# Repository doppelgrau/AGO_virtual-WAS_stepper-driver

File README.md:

# AGO_virtual-WAS_stepper-driver

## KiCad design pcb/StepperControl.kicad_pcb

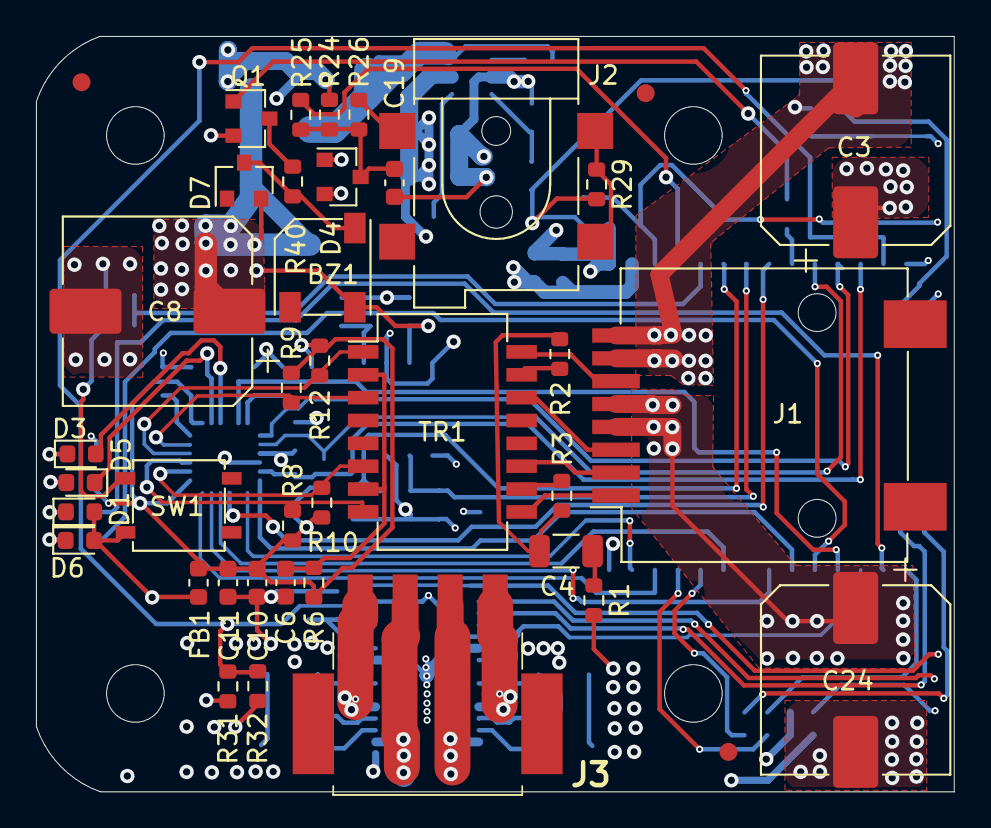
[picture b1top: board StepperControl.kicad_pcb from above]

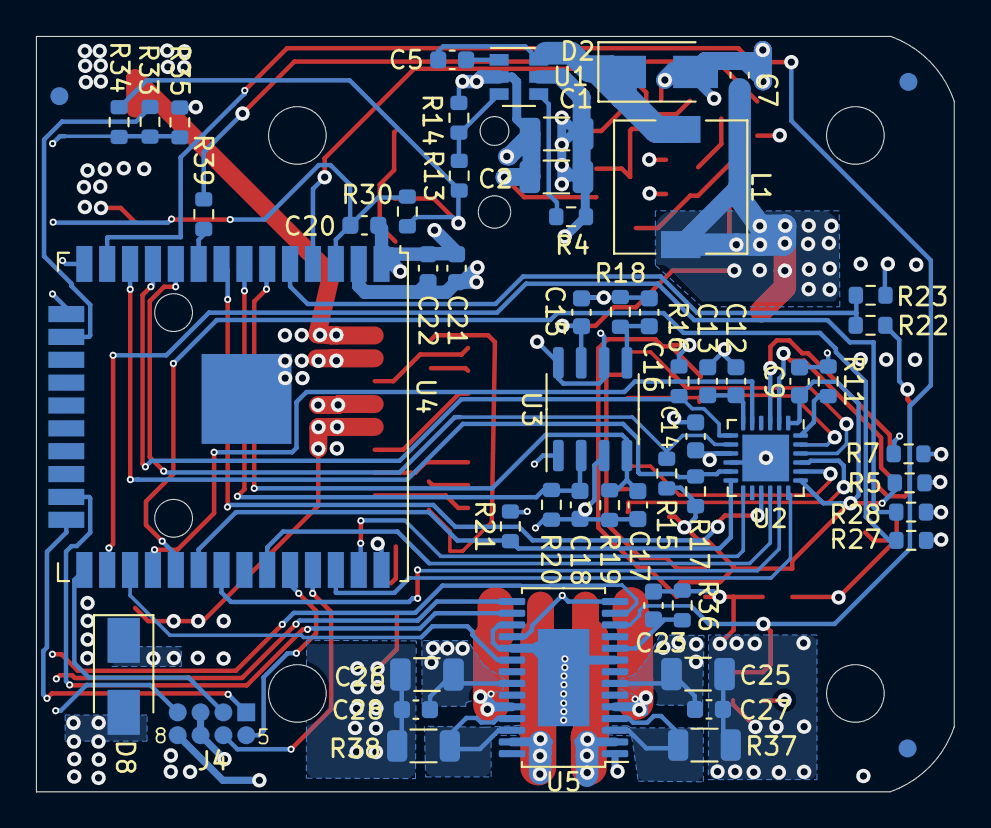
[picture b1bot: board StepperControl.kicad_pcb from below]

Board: 4 copper layers, 51.0 x 42.0 mm, 101 parts (57 on the bottom side), 72 nets.

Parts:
BZ1: SOUND-LD-BZEL-T56-0505; Loudity_SMT56
C1, C25, C26: CAP-X7R-1206-1uF-50V; C_1206_3216Metric
C2: CAP-X5R-1206-10uF-50V; C_1206_3216Metric
C3, C24: CAP-ALU-SMD-220uF-35V; CP_Elec_10x10
C4: CAP-X7R-1206-1nF-2kV; C_1206_3216Metric
C5, C6, C9, C11, C12, C14, C15, C20, C22, C27, C28: CAP-X7R-0603-100nF-50V; C_0603_1608Metric
C7, C10, C13, C21: CAP-X5R-0603-10uF-10V; C_0603_1608Metric
C8: CAP-ALU-SMD-1mF-10V; CP_Elec_10x10
C16, C17, C18, C19, C23: CAP-X7R-0603-1nF-50V; C_0603_1608Metric
D1: LED-0603-GREEN; LED_0603_1608Metric
D2, D8: DIO-STPS1L30; D_SMA
D3: LED-0603-YELLOW; LED_0603_1608Metric
D4, D7: DIO-BAT54S; SOT-23
D5: LED-0603-BLUE; LED_0603_1608Metric
D6: LED-0603-RED; LED_0603_1608Metric
FB1: IND-FER-0603-600OHM-0.5A; L_0603_1608Metric
FID1, FID2, FID3, FID4, FID5, FID6: Fiducial; Fiducial_1mm_Mask2mm
H1, H2, H3, H4: MountingHole; MountingHole_3.2mm_M3
J1: CONN-RJJS-88-143-E1V-039; RJJS-88-143-E1V-039
J2: CONN-PC-GK2.1-SMD; PC-GK2.1-SMD
J3: CONN-1702474; 1702474
J4: Conn_02x04_Prog_1.27; Conn_01x04_Test_Programming
L1: IND-7.3x7.3-22nH-1.0A; DE0703-22
Q1: BC849C; SOT-23
R1, R6: RES-0603-0; R_0603_1608Metric
R2, R3: RES-0603-56; R_0603_1608Metric
R4: RES-0603-2.7k; R_0603_1608Metric
R5, R14, R21: RES-0603-1.5k; R_0603_1608Metric
R7, R22, R25, R39: RES-0603-1k; R_0603_1608Metric
R8, R9, R10, R12: RES-0603-49.9; R_0603_1608Metric
R11: RES-0603-12k; R_0603_1608Metric
R13: RES-0603-4.7k; R_0603_1608Metric
R15, R16, R17: RES-0603-3.3k; R_0603_1608Metric
R18, R19, R20: RES-0603-100k; R_0603_1608Metric
R23, R24: RES-0603-220k; R_0603_1608Metric
R26, R29: RES-0603-10k; R_0603_1608Metric
R27, R40: RES-0603-270; R_0603_1608Metric
R28: RES-0603-120; R_0603_1608Metric
R30: RES-0603-47k; R_0603_1608Metric
R31, R33: RES-0603-8.2k; R_0603_1608Metric
R32: RES-0603-1.8k; R_0603_1608Metric
R34: RES-0603-15k; R_0603_1608Metric
R35: RES-0603-2.2k; R_0603_1608Metric
R36: RES-0603-68k; R_0603_1608Metric
R37, R38: RES-1206-0.1; R_1206_3216Metric
SW1: SW-SPST_TVCM04N; SW_SPST_TVCM04N
TR1: TRANS-PT61017PEL; Transformer_Ethernet_Bourns_PT61017PEL
U1: REG-BUCK-AOZ1282CI; SOT-23-6
U2: LAN8720A; QFN-24-1EP_4x4mm_P0.5mm_EP2.6x2.6mm
U3: SEN-MAG-KMZ60; SO-8_3.9x4.9mm_P1.27mm
U4: MCU-ESP32-WROOM-32U; ESP32-WROOM-32U
U5: MDR-STEPPER-BD63524AEFV; HTSSOP-28-1EP_4.4x9.7mm_P0.65mm_EP2.85x5.4mm

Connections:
+3V3: BZ1.1, C7.2, C8.1, C14.2, C15.2, C21.2, C22.2, D4.2, D5.2, D6.2, D7.2, FB1.1, J4.8, L1.2, R13.1, R21.2, R29.2, R30.2, R31.1, R34.1, SW1.1, U2.9, U3.1, U3.7, U4.2, U5.14, U5.18
+VDC: C1.1, C2.2, C3.1, C24.1, C25.1, C26.1, C27.1, C28.1, D8.1, J1.4, J1.5, R4.2, U1.5, U5.7, U5.22
-VDC: C1.2, C2.1, C3.2, C6.1, C7.1, C8.2, C9.2, C10.2, C11.2, C12.1, C13.1, C14.1, C15.1, C16.2, C17.2, C18.2, C19.2, C20.1, C21.1, C22.1, C23.1, C24.2, C25.2, C26.2, C27.2, C28.2, D2.2, D4.1, D8.2, J1.7, J1.8, J4.3, J4.7, Q1.2, R1.2, R7.1, R11.1, R14.1, R18.2, R19.2, R20.2, R23.1, R24.2, R32.2, R35.2, R36.1, R37.1, R38.1, U1.2, U2.10, U2.25, U3.3, U3.6, U3.8, U4.1, U4.15, U4.38, U4.39, U5.1, U5.9, U5.17, U5.19, U5.29
/+3V3LAN: C9.1, C10.1, C11.1, FB1.2, R5.1, R6.2, R8.2, R9.2, R10.2, R12.2, R15.2, R16.2, R17.2, U2.1, U2.19
/EMAC_CLK_OUT_180:GPIO17: U2.5, U4.28
/EMAC_RXD0:GPIO25: R15.1, U2.8, U4.10
/EMAC_RXD1:GPIO26: R16.1, U2.7, U4.11
/EMAC_RX_CRS_DV:GPIO27: R17.1, U2.11, U4.12
/EMAC_TXD0:GPIO19: U2.17, U4.31
/EMAC_TXD1:GPIO22: U2.18, U4.36
/EMAC_TX_EN:GPIO21: U2.16, U4.33
/MDC:GPIO23: U2.13, U4.37
/MDIO: R21.1, U2.12, U4.30
/PHY_RST:: U2.15, U4.8
/RD+: R9.1, TR1.3, U2.23
/RD-: R12.1, TR1.1, U2.22
/TD+: R8.1, TR1.8, U2.21
/TD-: R10.1, TR1.6, U2.20
unnamed: BZ1.2, D7.3, R40.1
unnamed: C4.1, R2.2, R3.2
unnamed: C4.2, R1.1
unnamed: C5.1, D2.1, L1.1, U1.6
unnamed: C5.2, U1.1
unnamed: C6.2, R6.1, TR1.2, TR1.7
unnamed: C12.2, C13.2, U2.6
unnamed: C16.1, R18.1, U3.5
unnamed: C17.1, R19.1, U3.4, U4.6
unnamed: C18.1, R20.1, U3.2, U4.7
unnamed: C19.1, D4.3, R24.1, R25.1, R26.1
unnamed: C20.2, J4.4, R30.1, U4.3
unnamed: C23.2, R36.2, U5.10
unnamed: D1.1, U2.2
unnamed: D1.2, R5.2
unnamed: D3.1, R7.2
unnamed: D3.2, U2.3
unnamed: D5.1, R28.1
unnamed: D6.1, R27.1
unnamed: J1.1, TR1.9
unnamed: J1.2, TR1.11
unnamed: J1.3, TR1.14
unnamed: J1.6, TR1.16
unnamed: J2.1, R29.1
unnamed: J2.2, R26.2
unnamed: J3.1, U5.5
unnamed: J3.2, U5.2
unnamed: J3.3, U5.27
unnamed: J3.4, U5.24
unnamed: J4.1, U4.24
unnamed: J4.2, U4.25
unnamed: J4.5, U4.34
unnamed: J4.6, U4.35
unnamed: Q1.1, R39.1
unnamed: Q1.3, R40.2
unnamed: R2.1, TR1.15
unnamed: R3.1, TR1.10
unnamed: R4.1, U1.4
unnamed: R11.2, U2.24
unnamed: R13.2, R14.2, U1.3
unnamed: R22.1, R23.2, U4.5
unnamed: R22.2, SW1.2
unnamed: R25.2, U4.4
unnamed: R27.2, U4.29
unnamed: R28.2, U4.26
unnamed: R31.2, R32.1, U4.13, U5.12
unnamed: R33.1, R34.2, R35.1, U5.13
unnamed: R33.2, U4.16
unnamed: R37.2, U5.3, U5.4
unnamed: R38.2, U5.25, U5.26
unnamed: R39.2, U4.9
unnamed: U4.14, U5.15
unnamed: U4.23, U5.16
unnamed: U4.27, U5.20

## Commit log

2021-08-21 Initial import Hardware
2021-12-19 Changes in the case
2021-12-19 Changes on the PCB
